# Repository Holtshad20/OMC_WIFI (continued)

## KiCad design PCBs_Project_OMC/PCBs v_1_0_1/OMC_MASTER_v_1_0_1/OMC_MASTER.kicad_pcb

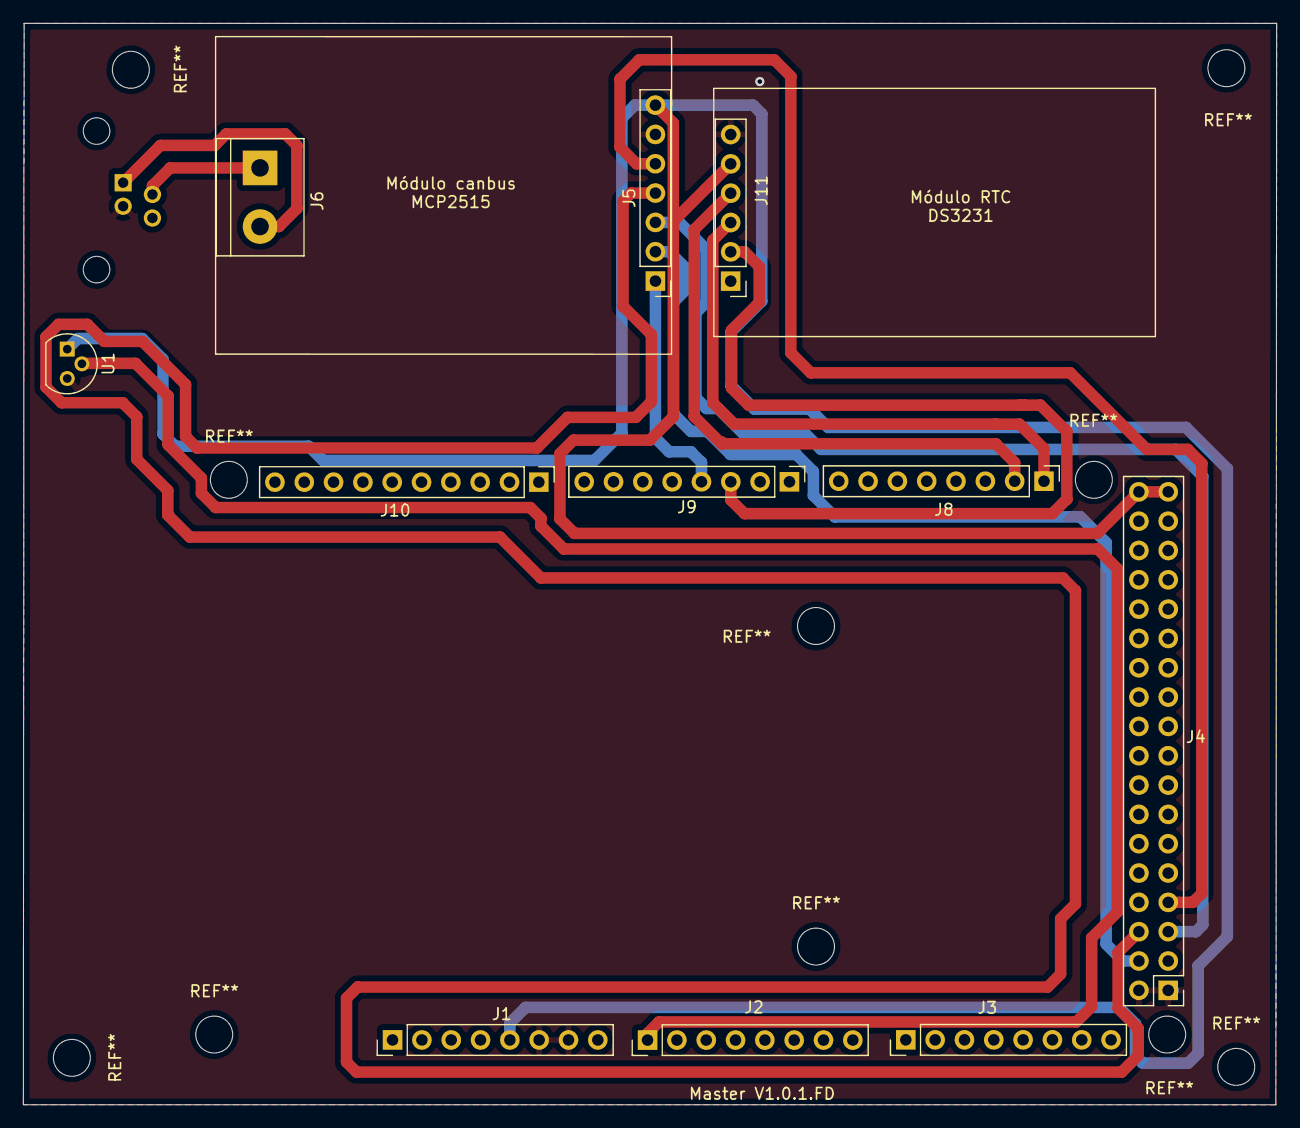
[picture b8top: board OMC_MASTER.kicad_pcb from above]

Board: 2 copper layers, 108.6 x 93.7 mm, 12 parts (1 on the bottom side), 13 nets.

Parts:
J1: Conn_01x08_Female_power; PinHeader_1x08_P2.54mm_Vertical
J2: Conn_01x08_Female_analog1; PinHeader_1x08_P2.54mm_Vertical
J3: Conn_01x08_Female_analog2; PinHeader_1x08_P2.54mm_Vertical
J4: Conn_02x18_Odd_Even; PinHeader_2x18_P2.54mm_Vertical
J5: Conn_01x07_Female_canbus; PinHeader_1x07_P2.54mm_Vertical
J6: Conn_01x02_Female_canbus; TerminalBlock_bornier-2_P5.08mm
J7: RJ14; RJ14_Connfly_DS1133-S4_Horizontal
J8: Conn_01x08_Female_digital3; PinHeader_1x08_P2.54mm_Vertical
J9: Conn_01x08_Female_digital2; PinHeader_1x08_P2.54mm_Vertical
J10: Conn_01x10_Female_digital1; PinHeader_1x10_P2.54mm_Vertical
J11: Conn_01x06_Female_clock; PinHeader_1x06_P2.54mm_Vertical
U1: LM35-LP; TO-92

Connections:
+5V: J1.5, J4.35, J4.36, J5.7, J11.5, U1.1
CS: J4.7, J5.5
GND: J1.6, J1.7, J4.1, J4.2, J5.6, J7.3, J11.6, U1.3
H: J6.2, J7.1
INTERRUPT: J5.1, J9.4
L: J6.1, J7.2
MISO: J4.6, J5.4
MOSI: J4.5, J5.3
SCK: J4.4, J5.2
SCL: J8.1, J11.3
SDA: J8.2, J11.4
SQW: J9.3, J11.2
TEMP: J2.1, U1.2

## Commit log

2022-02-04 Agregado:
    Diagramas esquematicos y de PCB del proyecto OMC, como referencia.
2022-02-07 Create voltaje_v1.ino
    Creado primer archivo de prueba
2022-02-11 Creados archivos iniciales para PCB
    Se crearon 2 archivos para trabajar en paralelo
2022-02-11 Creación nuevo documento KiCad
    - 2 archivos de KiCad
    + Archivo de KiCad para trabajar en conjunto
2022-02-11 Actualización Esquemático
    + Módulo ZMPT101B
    + Módulo ACS712
    + ESP32 DevKitv1
    + Fuente de alimentación
    + Módulo Relay
2022-02-14 ADDED
    +6PCV03006
2022-02-14 Actualización esquemático y PCB
    + Modificación del esquemático
    + Adición de footprints
    + Circuito amplificador para el relay
    + Modelo PCB del ZMPT101B
    + Adición de Librerías
2022-02-15 Reestructuración PCB
    > Cambio de posiciones
    + Anexar medidas
    - Eliminar LM741
2022-02-15 Actualización PCB
    + Medidas de ZMPT101B
    + Medidas Módulo Relay
2022-02-16 Actualización PCB
    + Medidas ACS712
    - Conexión 5V al switch
2022-02-16 Adición código de AutoConnect
2022-02-16 Actualización PCB
    + Pistas digitales
    > Modificación de Tags
    > Rediseño de la PCB
2022-02-17 Actualización PCB
    +Plano de Tierra
    > Rediseño PCB para utilizar un solo conector
    > Redistribución de pistas
2022-02-18 Actualización PCB
    + Jumper para ACS
    + Fusible
    > Rediseño de la PCB
2022-02-21 Diseño PCB
    + Archivos Gerber y Drill
    - Divisor de tensión del ACS712
2022-02-21 Actualización código AutoConnect
2022-02-21 Creación código prueba AD
    Este código lee un puerto AD y envía la lectura a través de comunicación serial.
2022-02-22 Diseño PCB
    > Modificación de dimensiones ESP32 Devkit V1 en PCB.
    > Modificadas las dimensiones de la placa.
    + Pistas entre puntas de fusible para aumentar área de contacto con soldadura.
    > Generados nuevos archivos gerber
2022-02-22 Actualización PCB
    > Actualización esquemático.
2022-02-22 Modificación PCB
    > Redimensionamiento Relay
    > Redimensionamiento ACS
2022-02-22 Actualización AutoConnect
    + Datos iniciales /ap_config
2022-02-23 Actualización PCB
    + Pista de potencia F. Cu
2022-02-23 AutoConnect
    > Modificación portal web
2022-02-24 Actualizaciónj AutoConnect
    > Actualización página web post-configuración
2022-02-25 Código de medidas analógicas
    + Nuevo código para la medición de corriente y voltaje sin uso de librerías:
    Las lecturas de voltaje están bien, se desvían aproximadamente +-3V del valor real.
    Voltajes inferiores a 60V se deben despreciar, se lee puro ruido.
    La lectura de corriente está cerca de lo real, pero le falta refinar -> Definir una mejor escala.
    El ruido afecta mucho las lecturas de corriente, más que nada cuando se trata de corrientes inferiores a 1/2 A.
2022-02-25 Actualización AutoConnect
    + Expresiones regulares
    + Libreria para detección de expresiones regulares
2022-02-28 Actualización AutoConnect
    + Código de verificación de credenciales
2022-03-02 Actualización código medidas analógicas
    + Actualización del promedio de mediciones cada 1000 muestras.
    > Cambio en factor de escala para voltajes.
    Aún falta por hacer pruebas con rangos 140 - 210 V y 210 - 240 V
    Aún falta por hacer pruebas con rango 0.3 - 15 A
2022-03-03 Creación del código para relay
    Inicio del código para comportamiento del relay, actualmente es solo una copia de lecturasAnalogicas.ino
2022-03-03 Actualización código Relay
    Modificación del código para que funcione con valores enviados por serial en lugar de trabajar con pulsador
2022-03-03 Actualización código Relay
    + Inclusión de timer: ocurre una interrupción cada segundo, el programador elige la cantidad de segundos necesarios para volver a permitir el paso de corriente.
    >> Se requiere combinar código con medidas analógicas para comprobar buen comportamiento del timer.
2022-03-03 Actualización AutoConnect
    > Modificación página web
2022-03-04 Reestructuración Repositorio
    > Reestructuración del respositorio para mayor orden y legibilidad
    + Creación de README.md
2022-03-08 Actualización AutoConnect
    > Modificación páginas web
    + Guardado de SSID
2022-03-09 Actualización AutoConnect
    + Guardar clave
    + Resetear credenciales de fábrica
2022-03-11 Actualización AutoConnect
    > Pequeñas modificaciones de comentarios
2022-03-11 Actualización AutoConnect
    + Introducción dirección IP del servidor
    + Función setup de AutoConnect
2022-03-14 Actulización AutoConnect
    + Chip ID
    + Archivo para configurar FreeRTOS
2022-03-16 Actualización FreeRTOS
    > Combinación Códigos AutoConnect y lectura analógica
2022-03-17 Creación código pruebas MQTT
    + Código para probar comunicación bidireccional MQTT.
2022-03-17 Actualización FreeRTOS
    + Tareas de AutoConnect y medición analógica en conjunto
2022-03-17 Código para obtener MAC
    + Código para obtener los últimos 3 bytes de la dirección MAC como String
2022-03-18 Actualización Relay
    > Adaptación a FreeRTOS
2022-03-18 Actualización AutoConnect y FreeRTOS
    + Página de control del relé
2022-03-18 Actualización código Relay
    + Timer FreeRTOS
    Nota: comportamiento errático, falta mejorar
2022-03-21 Actualización Autoconnect
    > Página para cortar el suministro
2022-03-22 ACtualización AutoConnect
    > Página de corte de suministro
2022-03-22 Actualización código Relay y Código presentación
    > Actualización código de relay. Implementación lista para poder utilizarse en código final.
    > Cambio en factor de escala en medidas analógicas
    + Código que integra medición, relay y comunicación con servidor usado para la presentación
2022-03-23 Diseño PCB 1.1
    > Modificación esquemático
2022-03-24 Actualización código con FreeRTOS
    > Autoconnect con mediciones y Relay
2022-03-24 Actualización FreeRTOS
    > Combinación AutoConnect, mediciones, relay y MQTT
2022-03-28 Librerías para clavijas
    + Esquemático y footprint de clavija macho
    + Esquemático y footprint de clavija hembra
2022-03-28 PCB v1.1
    >Actualización esquemático y PCB
2022-03-30 Actualización PCB v1.1
    + Alimentación (Input/Output)
2022-03-31 Actualización PCB
    > Divisores de tensión
    > Nuevos Gerbers
2022-04-05 Actualización AutoConnect
    + Modificación Labels en página principal
    + Modificación de ítems que aparecen en la página principal
2022-04-06 Actualización AutoConnect
    + Borrar toda la memoria NVS
    + Página web de autenticación para configuración del ESP32
2022-04-07 Modificación AutoConnect
    > Modificación menú de configuración
2022-04-08 Actualización Autoconnect
    > Modificación página Suministro Eléctrico
2022-04-08 Actualización AutoConnect
    > Modificación página Suministro Eléctrico
    + Librería modificada AutoConnect
2022-04-08 Actualización PCB
    + Construcción V1.2
2022-04-11 Actualización AutoConnect
    > Modificación página web del Suministro Eléctrico
2022-04-11 Actualización PCB y AutoConnect
    > Cambios en código para compatibilidad entre clientes MQTT
    > Agregados modelos 3D Fuente y Relay
2022-04-12 Actualización PCB y nueva librería para plug macho
2022-04-12 Actualización FreeRTOS
    > Cambios del merge
2022-04-13 Librerías OMC KiCad
    > Modificación clavijas hembras
    > Footprint y esquemático PZEM-004T-100A
2022-04-13 Actualización PCB y Librerías
2022-04-19 Actualización Footprints
    > Modificación Fermale Plug
2022-04-19 Actualización PCB
2022-04-20 Actualización PCB
    Diseño casi final
2022-04-22 Interrupción de Touch Button
2022-04-26 Modelos 3D de clavijas
    +Creación de modelos 3D para Clavijas
2022-05-02 Actualización PCB
    > Creación de Versión 1.3 con espacio para toroide
2022-05-03 Actualización FreeRTOS
    + Implementación tareas de los leds
2022-05-10 Creación de versión 1.4 PCB
    > Cambio en diseño para paso de cable por toroide.
2022-05-11 Actualización FreeRTOS
2022-05-18 Primer código pruebas PZEM
2022-05-23 Creación de nuevas librerías conectores AC
    Creación de librería 2D para conectores macho y hembra para AC
2022-05-24 Actualización PCB
    Nuevo diseño (v1.5) con piezas nuevas para AC
2022-05-25 Actualización PCB
    > Cambio en polaridad de transistor
    > Cambio en planos de tierra y B.Mask
    > Cambio en librería de conector hembra AC
2022-05-31 Creación de GERBERS PCB v1.5
    Se incluyen cambios pequeños en la PCB:
    > Cambio al transistor MMBT3904
    > Cambio en puntos de soldadura para los cables del toroide.
2022-06-01 Actualización Código
    + Archivos .cpp y .h
2022-06-07 Actualización código .cpp y .h
    + Código MQTT
    + Código Leds
    + Código TouchSensor
2022-06-08 Actualización Código .cpp y .hpp
    + Integración de todos los códigos
2022-06-14 Actualización Código
    + Modificación página web ESP
2022-06-15 Código Servidor
    Primero commit de código servidor
2022-06-22 Actualización Código v1.0
2022-06-28 Update flows.json
    Adición de tabla
2022-06-28 Actualización Código v1.0
    > Modificación código MQTT
2022-06-29 Modificación Código OMC v1.0
    > Actualización código MQTT
2022-07-06 Actualización Código MQTT
    > Modificación código para elegir el número de OMC
2022-07-12 Creación Código v1.5
    > Modificación para incluir PZEM
2022-07-19 Actualización código
    Cambio de pines versión 1.55
2022-07-19 Actualización servidor
2022-08-03 Creación de versión 1.6 PCB
2022-08-23 Update OMC_WIFI_mqtt.cpp
    El código de reinicio de energía estaba comentado
2022-08-24 Cambios código OMC
    > Cambió mensaje de bienvenida a pagina de AutoConnect
    > Un cambio de IP de servidor activa timer de MQTT en lugar de llamar a connectToMQTT()
    > Se arregló la manera de hacer reinicio del contador de energia declarando otro objeto pzem con la misma dirección
    > No se intenta conectar a MQTT si se tiene 0.0.0.0 como IP
    > Se agregó la el algoritmo de desconexión/rechazo al recibir el [ID]99
2022-08-25 Actualización código
    > En lugar de enviar estado del relay al servidor, se enviará el estado del dispositivo:
    0 OPERATIVO
    1 TIEMPO ESPERA
    2 BLOQUEO MANUAL
    3 BAJO VOLTAJE
    4 ALTO VOLTAJE
2022-08-25 Update flows.json
    Actualización código de servidor para compatibilidad con cambios en OMC.
2022-08-30 Actualización código
    > No retener mensajes MQTT en servidor
2022-08-30 OMC Final Code 1.5
    + Enviar IP al servidor
    + Apagar AP con conexión al servidor
2022-08-30 Actualización código
    + Testamento
2022-08-30 OMC Code 1.5
    + Uptime
    + Guardado de control manual
2022-08-31 Final OMC Code v1.5
    + Reinicio retardado (random y cpnectado al servidor)
2022-09-02 OMC Final Code v1.5
    > Cambio timers para evitar crash del dispositivo 01
2022-09-02 Actualización servidor y código
    >Cambios servidor
    > Cambio para evitar problemas con periodo 0 en timerSecundario
    > Intento de arreglar problema al reiniciar equipo
2022-09-06 OMC Finalk COde v1.5
    > Arreglar reinicio
    > Arreglar lectura
2022-09-07 OMC Final Code v1.5
    > Tiempo de aplicación móvil
    + Varios corte de corriente
2022-09-09 OMC Final Code v1.5
    + Estado OMC 6 - Bloqueo Automático por exceso de fallas de Alta Corriente
2022-09-13 OMC Final Code v1.5
    > Parpadeo de los leds
    > Modificación falla por corriente
2022-09-15 Actualización código OMC
    > Se modificó una parte del código de MQTT. Había algo que funcionaba por obra y gracia del Espíritu Santo (por alguna razón dentro de un arreglo de 4 caracteres cabían 6 caracteres). Esto dio proble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
    + Se agregaron mensajes para notificar si llegó un mensaje MQTT en el OMC
2022-09-15 Actualización código
    + Agregar comentarios
2022-09-21 OMC Final Code v1.5
    > Restart issues
2022-10-31 OMC Final Code v1.5
    + Restart Fix
